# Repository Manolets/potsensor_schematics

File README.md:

# Pot Sensor Schematics

This repo contains the KiCad project files for a battery powered plant sensor.

Features a capacitative soil moisture sensor, a temperature and humidity sensor. To export the data, it has a 2.4GHz radio antenna and a USB-C connector for charging the battery and programming the ESP32.

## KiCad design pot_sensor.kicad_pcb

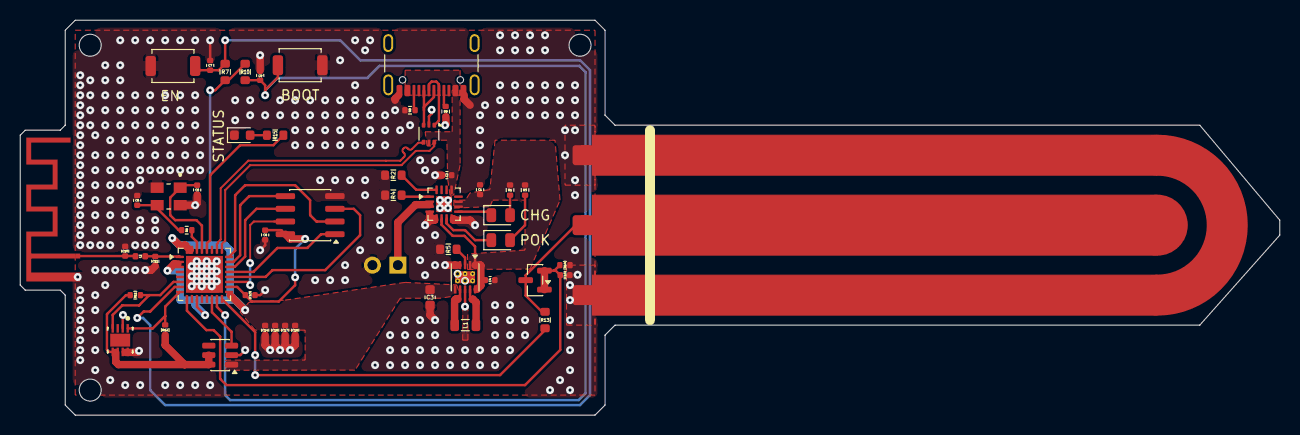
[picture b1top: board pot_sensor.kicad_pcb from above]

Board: 2 copper layers, 126.0 x 39.5 mm, 52 parts (1 on the bottom side), 43 nets.

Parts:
A1: 2.4GHz; 2.4GHz_Antenna
C1: 4µ7; C_0402_1005Metric
C2, C15: 1u; C_0402_1005Metric
C3: 22µ; C_0603_1608Metric
C4, C13, C14: 10µ; C_0402_1005Metric
C5, C6: 30p; C_0402_1005Metric
C7, C8, C9, C16, C17, C18: 100n; C_0402_1005Metric
C10: 3p9; C_0402_1005Metric
C11: 4p9; C_0402_1005Metric
C12: Soil Hum Sensor; Capacitative Sensor
D1: RED; LED_0805_2012Metric
D2: GREEN; LED_0805_2012Metric
D3: BAT54; SOT-23
D4: YELLOW; LED_0603_1608Metric
J1: USB_C_Receptacle_USB2.0_14P; USB_C_Receptacle_GCT_USB4105-xx-A_16P_TopMnt_Horizontal
JSTconnector1: LiionBatt; PinHeader_1x02_P2.54mm_Horizontal
L1: 2µ2; L_0805_2012Metric
L2: 1n84; L_0402_1005Metric
R1, R3: 1K; R_0402_1005Metric
R2: 1K78; R_0603_1608Metric
R4, R7, R10: 10K; R_0603_1608Metric
R5: 36k5; R_0603_1608Metric
R6: 22R; R_0402_1005Metric
R8, R9: 5K1; R_0402_1005Metric
R11, R12: 4k7; R_0402_1005Metric
R13: 10k; R_0603_1608Metric
R14: 510k; R_0402_1005Metric
R15: 60R; R_0603_1608Metric
SW1: EN; SW_SPST_TS-1088-xR025
SW2: BOOT; SW_SPST_TS-1088-xR025
U1: ESP32-C3; QFN-32-1EP_5x5mm_P0.5mm_EP3.7x3.7mm
U2: BQ24074RGT; VQFN-16-1EP_3x3mm_P0.5mm_EP1.6x1.6mm
U3: TPS63900; WSON-10-1EP_2.5x2.5mm_P0.5mm_EP1.2x2mm_ThermalVias
U4: W25Q80DVSNIG; SOIC-8_3.9x4.9mm_P1.27mm
U5: USBLC6-2P6; SOT-666
U7: HDC3020DEFR; DEF0008A-IPC_B
U8: TPS22917DBV; SOT-23-6
Y1: ABM8-40MHZ; XTAL_ABM8-40.000MHZ-10-1-U-T

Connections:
3V3SPI: C8.1, C13.1, U1.18 (VDD_SPI), U4.8 (VCC)
+3V3: C3.1, C14.2, C16.2, C17.2, C18.2, R7.1, R10.1, U1.2 (VDD3P3), U1.3 (VDD3P3), U1.11 (VDD3P3_RTC), U1.17 (VDD3P3_CPU), U1.31 (VDDA), U1.32 (VDDA), U3.6 (VOUT), U8.1 (VIN)
/1MHz_PWM: R13.2, U1.16 (GPIO10)
/ADC_CH4: C15.2, D3.1 (K), D3.2 (A), R14.2, U1.9 (MTMS)
/BOOT_PIN: C9.1, R10.2, SW2.2, U1.15 (GPIO9)
/SCL_line: R11.2, U1.6 (GPIO2), U7.4 (SCL)
/SDA_line: R12.2, U1.8 (GPIO3), U7.1 (SDA)
/USB_D+: U1.26 (GPIO19), U5.4 (I/O2)
/USB_D-: U1.25 (GPIO18), U5.6 (I/O1)
GND: A1.1 (GND), C1.2, C2.2, C3.2, C4.2, C5.2, C6.2, C7.2, C8.2, C9.2, C10.1, C11.2, C12.1 (GND), C13.2, C14.1, C15.1, C16.1, C17.1, C18.1, D4.1 (K), J1.A1 (GND), J1.A12 (GND), J1.B1 (GND), J1.B12 (GND), JSTconnector1.2, R2.1, R4.1, R5.2, R8.2, R9.2, R14.1, SW1.1, SW2.1, U1.33 (GND), U2.4 (~CE), U2.5 (EN2), U2.8 (VSS), U2.17 (VSS), U3.4 (CFG2), U3.5 (CFG3), U3.8 (GND), U3.11 (GND), U4.4 (GND), U5.2 (GND), U7.2 (ADDR), U7.7 (ADDR1), U7.8 (GND), U8.2 (GND), Y1.2 (GND), Y1.4 (GND__1)
unnamed: A1.2 (Feed), C10.2, L2.2
unnamed: C6.1, R6.1, Y1.3
unnamed: C12.2 (CIN), D3.3, R13.1
unnamed: D1.2 (A), R1.1
unnamed: D1.1 (K), U2.9 (~CHG)
unnamed: D2.2 (A), R3.1
unnamed: D2.1 (K), U2.7 (~PGOOD)
unnamed: D4.2 (A), R15.1
unnamed: J1.A5 (CC1), R9.1
unnamed: J1.B5 (CC2), R8.1
unnamed: J1.A6 (D+), J1.B6 (D+), U5.3 (I/O2)
unnamed: J1.A7 (D-), J1.B7 (D-), U5.1 (I/O1)
unnamed: JSTconnector1.1, U2.2 (BAT), U2.3 (BAT)
unnamed: C7.1, R7.2, SW1.2, U1.7 (CHIP_EN)
unnamed: U1.14 (GPIO8), U8.3 (ON)
unnamed: C11.1, L2.1, U1.1 (LNA_IN)
unnamed: U1.22 (SPICLK), U4.6 (CLK)
unnamed: U1.21 (SPICS0), U4.1 (~CS)
unnamed: U1.23 (SPID), U4.5 (DI/IO_{0})
unnamed: U1.19 (SPIHD), U4.7 (~HOLD/~RESET/IO_{3})
unnamed: U1.24 (SPIQ), U4.2 (DO/IO_{1})
unnamed: U1.20 (SPIWP), U4.3 (~WP/IO_{2})
unnamed: R15.2, U1.28 (U0TXD)
unnamed: C5.1, U1.29 (XTAL_N), Y1.1
unnamed: R6.2, U1.30 (XTAL_P)
unnamed: C1.1, C4.1, R1.2, R3.2, U2.6 (EN1), U2.10 (OUT), U2.11 (OUT), U3.1 (EN), U3.2 (SEL), U3.10 (VIN)
unnamed: R2.2, U2.16 (ISET)
unnamed: R4.2, U2.1 (TS)
unnamed: R5.1, U3.3 (CFG1)
unnamed: L1.2, U3.9 (LX1)
unnamed: L1.1, U3.7 (LX2)
Peripheral3V3: R11.1, R12.1, U7.5 (VDD), U7.6 (RESET_N), U8.5 (QOD), U8.6 (VOUT)
VIN_USB: C2.1, J1.A4 (VBUS), J1.A9 (VBUS), J1.B4 (VBUS), J1.B9 (VBUS), U2.13 (IN), U5.5 (VBUS)
